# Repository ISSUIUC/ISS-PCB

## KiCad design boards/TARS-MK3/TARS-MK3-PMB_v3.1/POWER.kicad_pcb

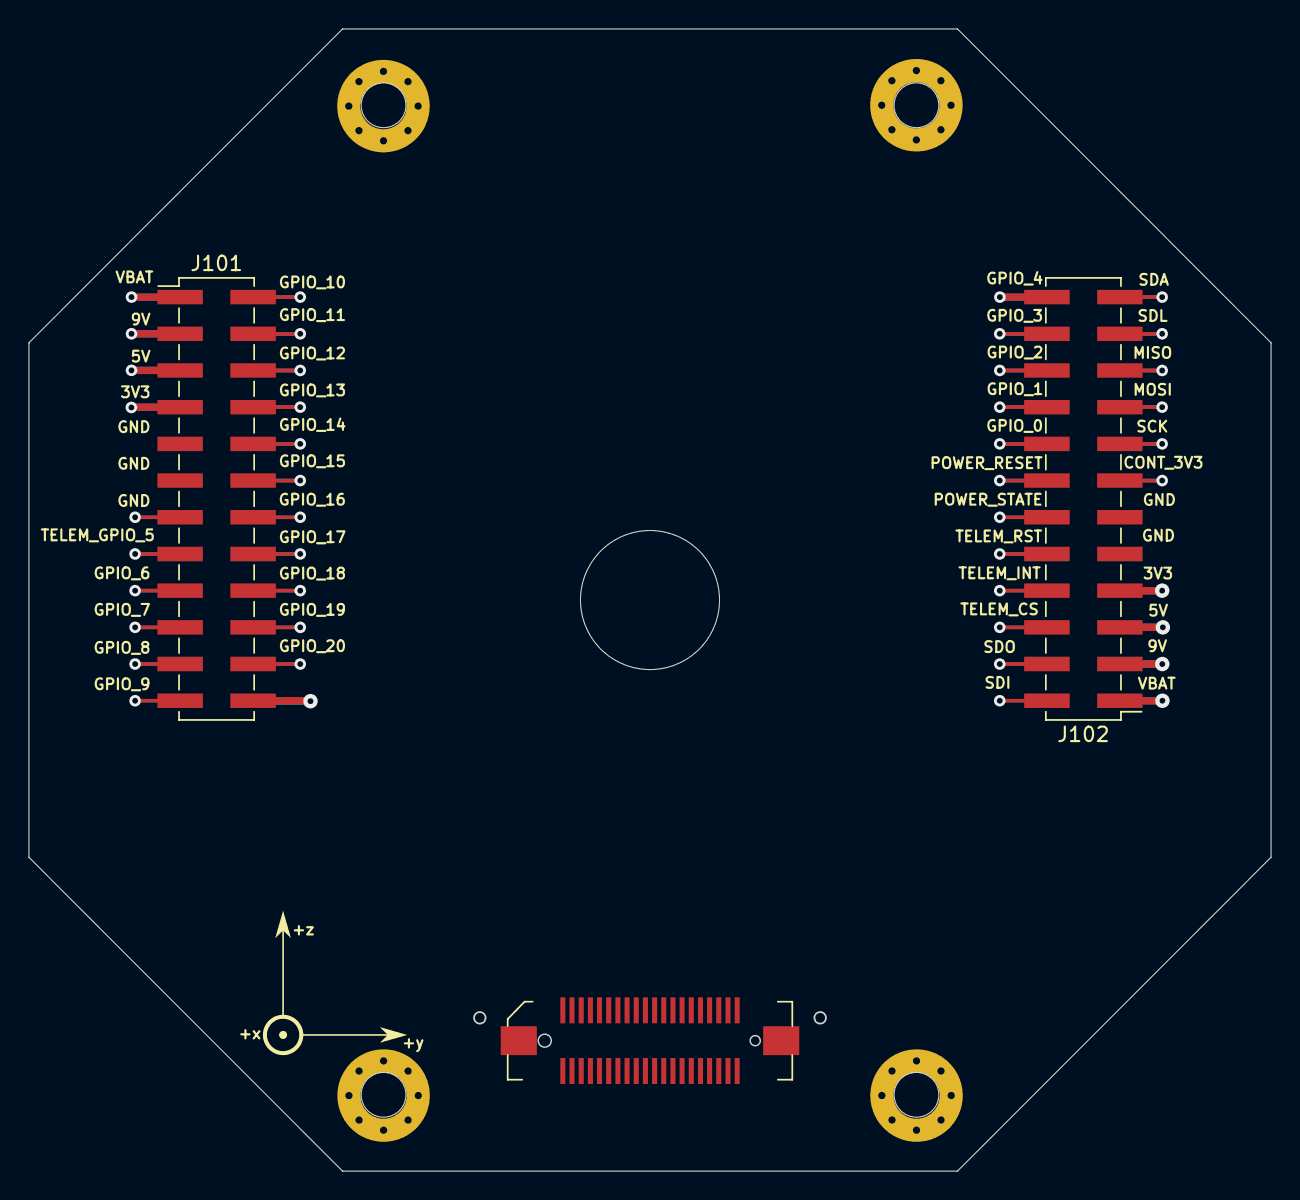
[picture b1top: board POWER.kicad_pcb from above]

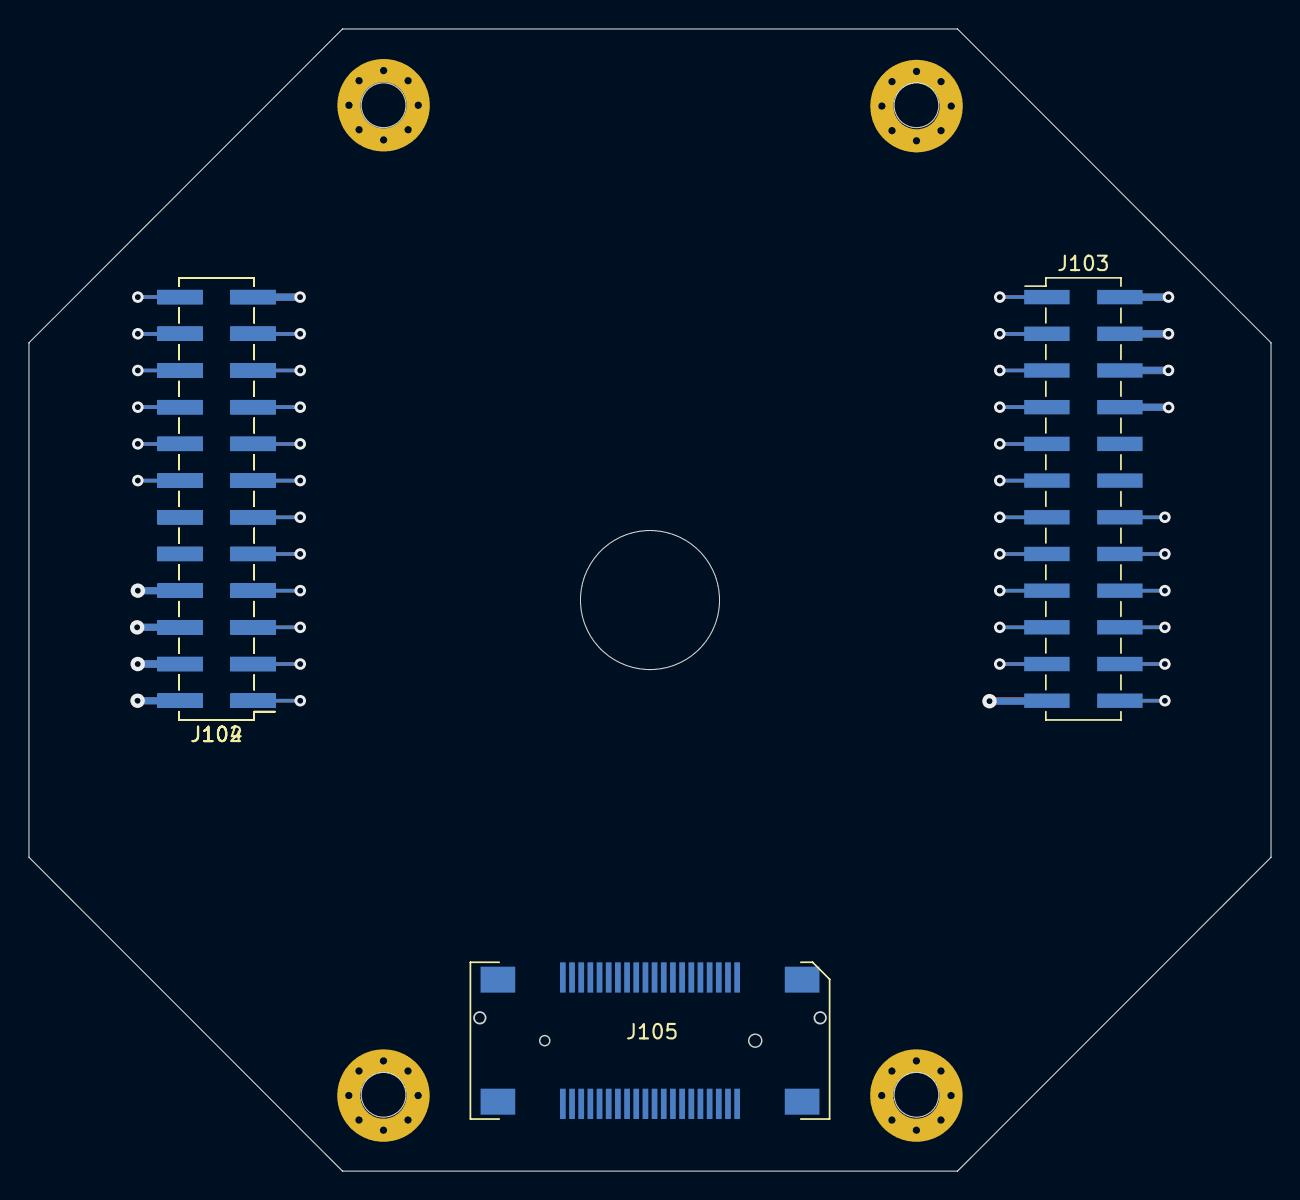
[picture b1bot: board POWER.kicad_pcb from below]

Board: 2 copper layers, 86.0 x 79.1 mm, 7 parts (4 on the bottom side), 41 nets.

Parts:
J101, J102, J102#2, J103, J104: Conn_02x12_Odd_Even; PinHeader_2x12_P2.54mm_Vertical_SMD
J105: Receptacle; 2091680401
J106: 536270474

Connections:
6V_AC_SERVO1: J102.24, J102#2.23, J104.23
6V_AC_SERVO2: J101.24, J103.23
/3V3: J101.7, J102.7, J102#2.8, J103.8, J104.8
/5V: J101.5, J102.5, J102#2.6, J103.6, J104.6
/9V: J101.3, J102.3, J102#2.4, J103.4, J104.4
/B2B_GPIO_8: J101.21, J103.22
/B2B_GPIO_9: J101.23, J103.24
/B2B_GPIO_10: J101.2, J103.1
/B2B_GPIO_11: J101.4, J103.3
/B2B_GPIO_12: J101.6, J103.5
/B2B_GPIO_13: J101.8, J103.7
/B2B_GPIO_14: J101.10, J103.9
/B2B_GPIO_15: J101.12, J103.11
/B2B_GPIO_16: J101.14, J103.13
/B2B_GPIO_17: J101.16, J103.15
/B2B_GPIO_18: J101.18, J103.17
/B2B_GPIO_19: J101.20, J103.19
/B2B_GPIO_20: J101.22, J103.21
/B2B_I2C_SCL: J102.21, J102#2.22, J104.22
/B2B_I2C_SDA: J102.23, J102#2.24, J104.24
/B2B_SPI_MISO: J102.19, J102#2.20, J104.20
/B2B_SPI_MOSI: J102.17, J102#2.18, J104.18
/B2B_SPI_SCK: J102.15, J102#2.16, J104.16
/B2B_UART_SDI: J102.2, J102#2.1, J104.1
/B2B_UART_SDO: J102.4, J102#2.3, J104.3
/CONT_3V3: J102.13, J102#2.14, J104.14
/CONT_GND: J101.13, J103.14
/GND: J101.9, J101.11, J102.9, J102.11, J102#2.10, J102#2.12, J103.10, J103.12, J104.10, J104.12
/POWER_RESET: J102.14, J102#2.13, J104.13
/POWER_STATE: J102.12, J102#2.11, J104.11
/SERVO1: J101.17, J103.18
/SERVO2: J101.19, J103.20
/TELEM_CS: J102.6, J102#2.5, J104.5
/TELEM_GPIO_1: J102.16, J102#2.15, J104.15
/TELEM_GPIO_2: J102.18, J102#2.17, J104.17
/TELEM_GPIO_3: J102.20, J102#2.19, J104.19
/TELEM_GPIO_4: J102.22, J102#2.21, J104.21
/TELEM_GPIO_5: J101.15, J103.16
/TELEM_INT: J102.8, J102#2.7, J104.7
/TELEM_RST: J102.10, J102#2.9, J104.9
/VBAT: J101.1, J102.1, J102#2.2, J103.2, J104.2

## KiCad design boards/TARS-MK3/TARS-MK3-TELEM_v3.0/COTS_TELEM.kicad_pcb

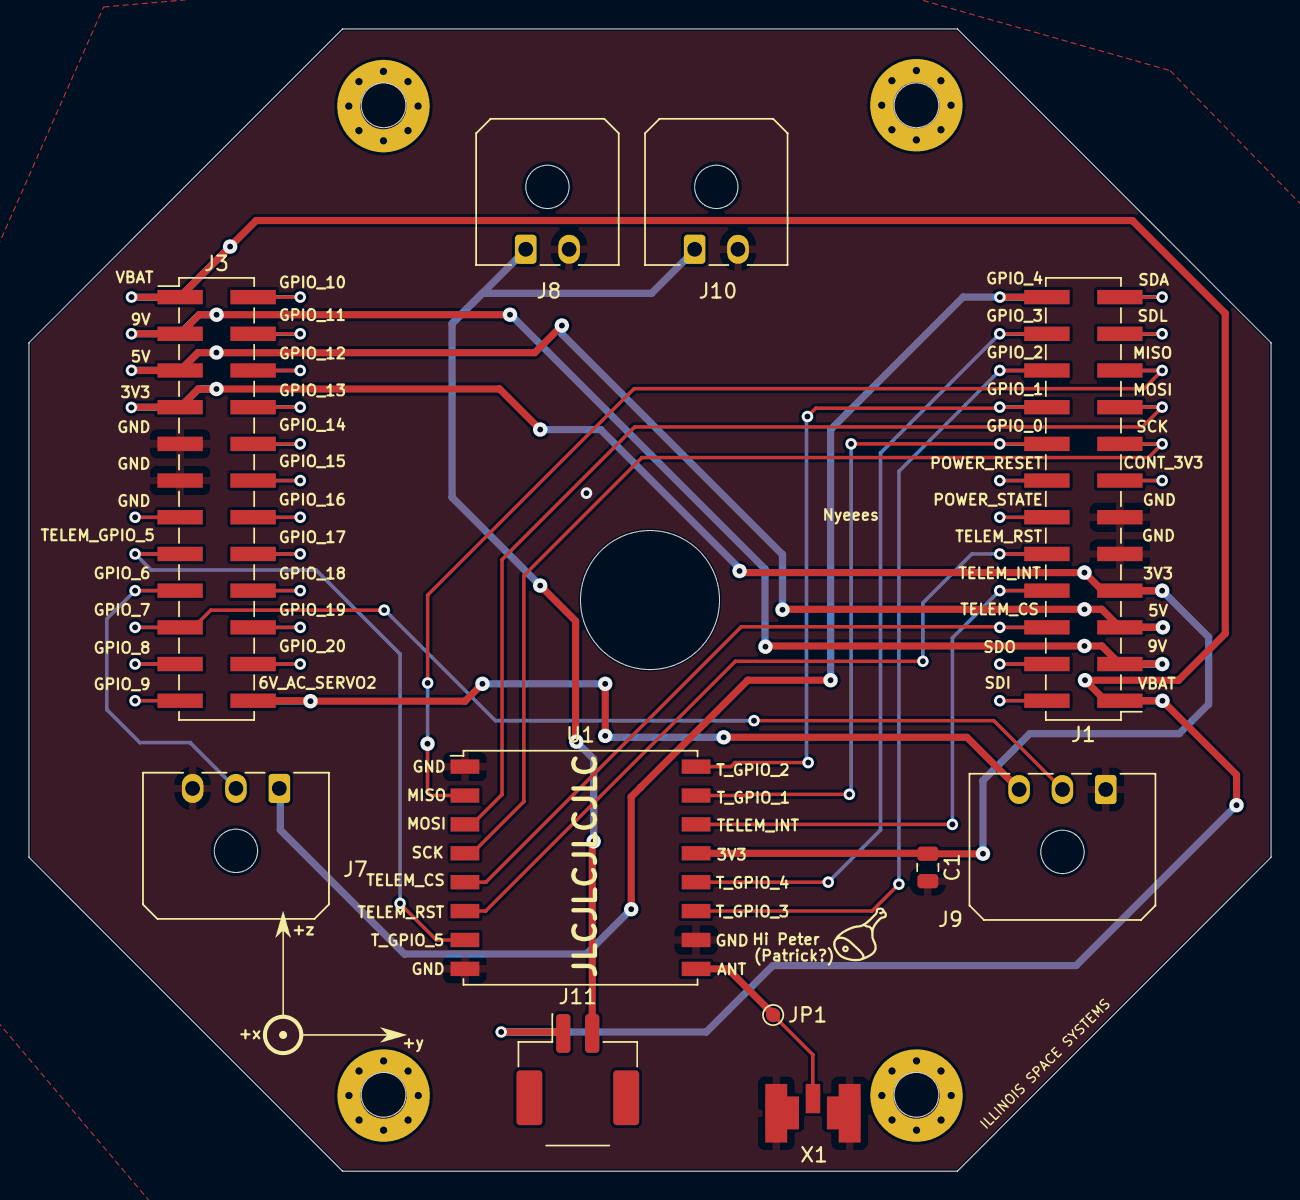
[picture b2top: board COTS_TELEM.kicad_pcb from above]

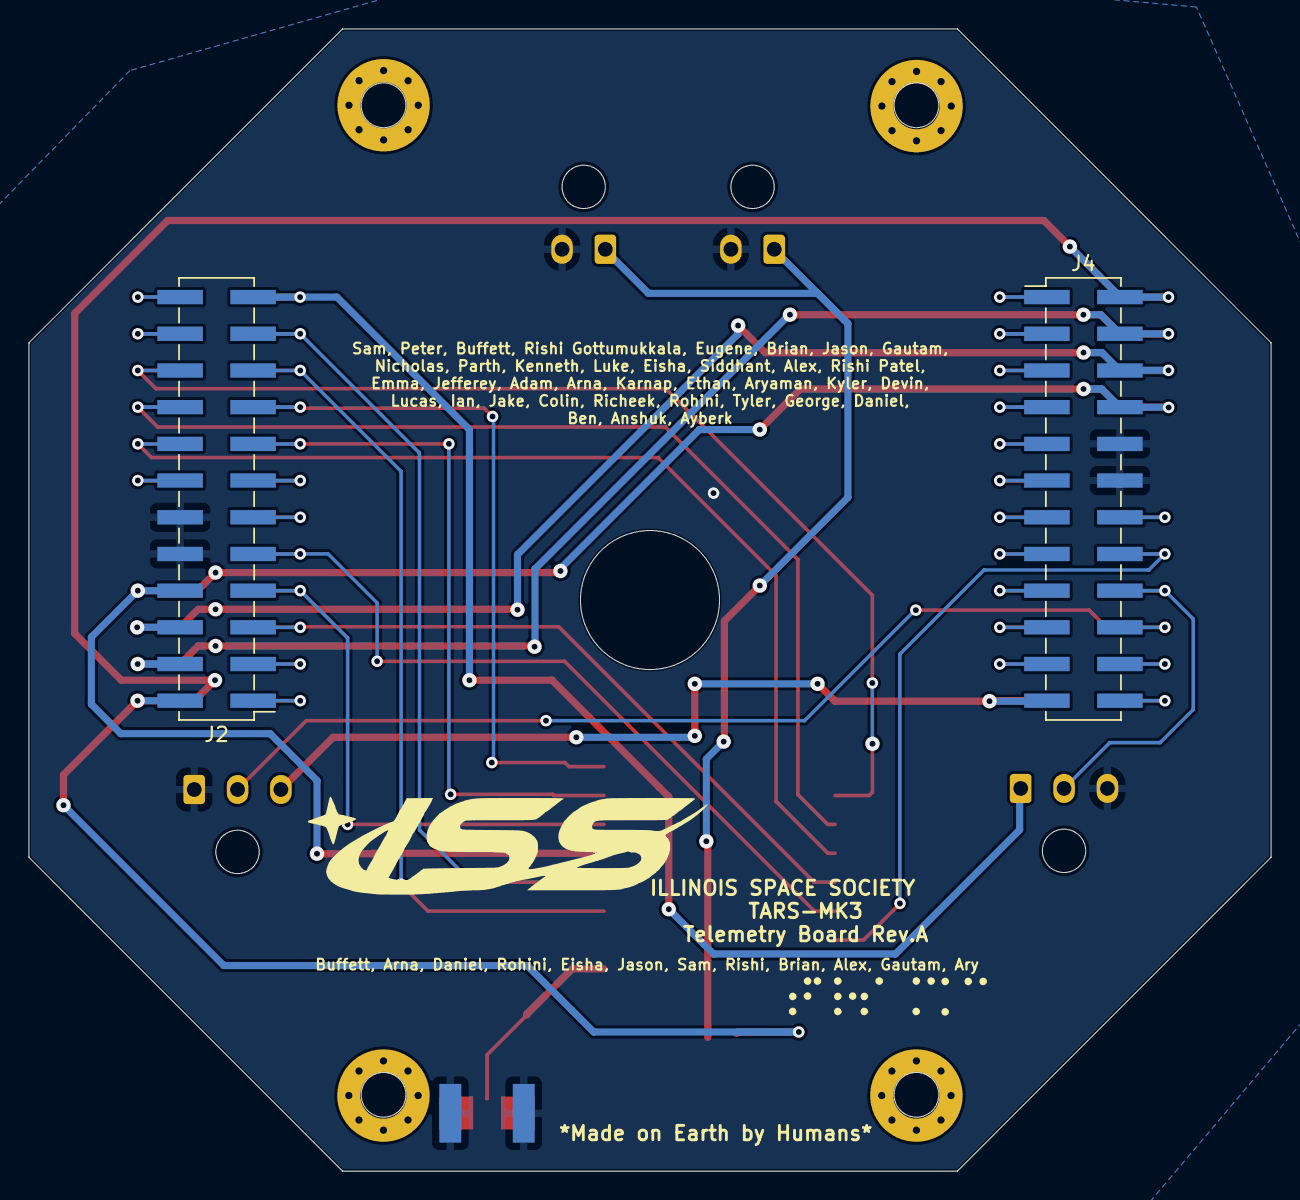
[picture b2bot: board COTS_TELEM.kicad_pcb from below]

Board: 2 copper layers, 86.0 x 79.1 mm, 13 parts (2 on the bottom side), 43 nets.

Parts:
C1: 10uF; C_0805_2012Metric
J1, J2, J3, J4: Conn_02x12_Odd_Even; PinHeader_2x12_P2.54mm_Vertical_SMD
J7, J9: Conn_01x03; Molex_Micro-Fit_3.0_43650-0300_1x03_P3.00mm_Horizontal
J8, J10: Conn_01x02; Molex_Micro-Fit_3.0_43650-0200_1x02_P3.00mm_Horizontal
J11: Conn_01x02; Molex_CLIK-Mate_502494-0270_1x02-1MP_P2.00mm_Horizontal
JP1: Conn_01x01_Female; TestPoint_Pad_D1.0mm
U1: RFM96W-433S2; HOPERF_RFM9XW_SMD
X1: uFL/SMA; uFL

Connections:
6V_AC_SERVO1: J1.24, J2.23, J7.1
6V_AC_SERVO2: J3.24, J4.23, J9.3
/3V3: C1.1, J1.7, J2.8, J3.7, J4.8, U1.13 (3.3V)
/5V: J1.5, J2.6, J3.5, J4.6
/9V: J1.3, J2.4, J3.3, J4.4
/B2B_GPIO_8: J3.21, J4.22
/B2B_GPIO_9: J3.23, J4.24
/B2B_GPIO_10: J3.2, J4.1
/B2B_GPIO_11: J3.4, J4.3
/B2B_GPIO_12: J3.6, J4.5
/B2B_GPIO_13: J3.8, J4.7
/B2B_GPIO_14: J3.10, J4.9
/B2B_GPIO_15: J3.12, J4.11
/B2B_GPIO_16: J3.14, J4.13
/B2B_GPIO_17: J3.16, J4.15
/B2B_GPIO_18: J3.18, J4.17
/B2B_GPIO_19: J3.20, J4.19
/B2B_GPIO_20: J3.22, J4.21
/B2B_I2C_SCL: J1.21, J2.22
/B2B_I2C_SDA: J1.23, J2.24
/B2B_SPI_MISO: J1.19, J2.20, U1.2 (MISO)
/B2B_SPI_MOSI: J1.17, J2.18, U1.3 (MOSI)
/B2B_SPI_SCK: J1.15, J2.16, U1.4 (SCK)
/B2B_UART_SDI: J1.2, J2.1
/B2B_UART_SDO: J1.4, J2.3
/CONT_3V3: J1.13, J2.14
/CONT_GND: J3.13, J4.14
/POWER_RESET: J1.14, J2.13
/POWER_STATE: J1.12, J2.11
/SERVO1: J3.17, J4.18, J7.2
/SERVO2: J3.19, J4.20, J9.2
/TELEM_CS: J1.6, J2.5, U1.5 (NSS)
/TELEM_GPIO_1: J1.16, J2.15, U1.15 (DIO1)
/TELEM_GPIO_2: J1.18, J2.17, U1.16 (DIO2)
/TELEM_GPIO_3: J1.20, J2.19, U1.11 (DIO3)
/TELEM_GPIO_4: J1.22, J2.21, U1.12 (DIO4)
/TELEM_GPIO_5: J3.15, J4.16, U1.7 (DIO5)
/TELEM_INT: J1.8, J2.7, U1.14 (DIO0)
/TELEM_RST: J1.10, J2.9, U1.6 (RESET)
/VBAT: J1.1, J2.2, J3.1, J4.2, J11.1
GND: C1.2, J1.9, J1.11, J2.10, J2.12, J3.9, J3.11, J4.10, J4.12, J7.3, J8.2, J9.1, J10.2, U1.1 (GND), U1.8 (GND), U1.10 (GND), X1.GND1, X1.GND2, X1.GND3, X1.GND4
unnamed: J8.1, J10.1, J11.2
unnamed: JP1.1, U1.9 (ANT), X1.ANTENNA (ANT)

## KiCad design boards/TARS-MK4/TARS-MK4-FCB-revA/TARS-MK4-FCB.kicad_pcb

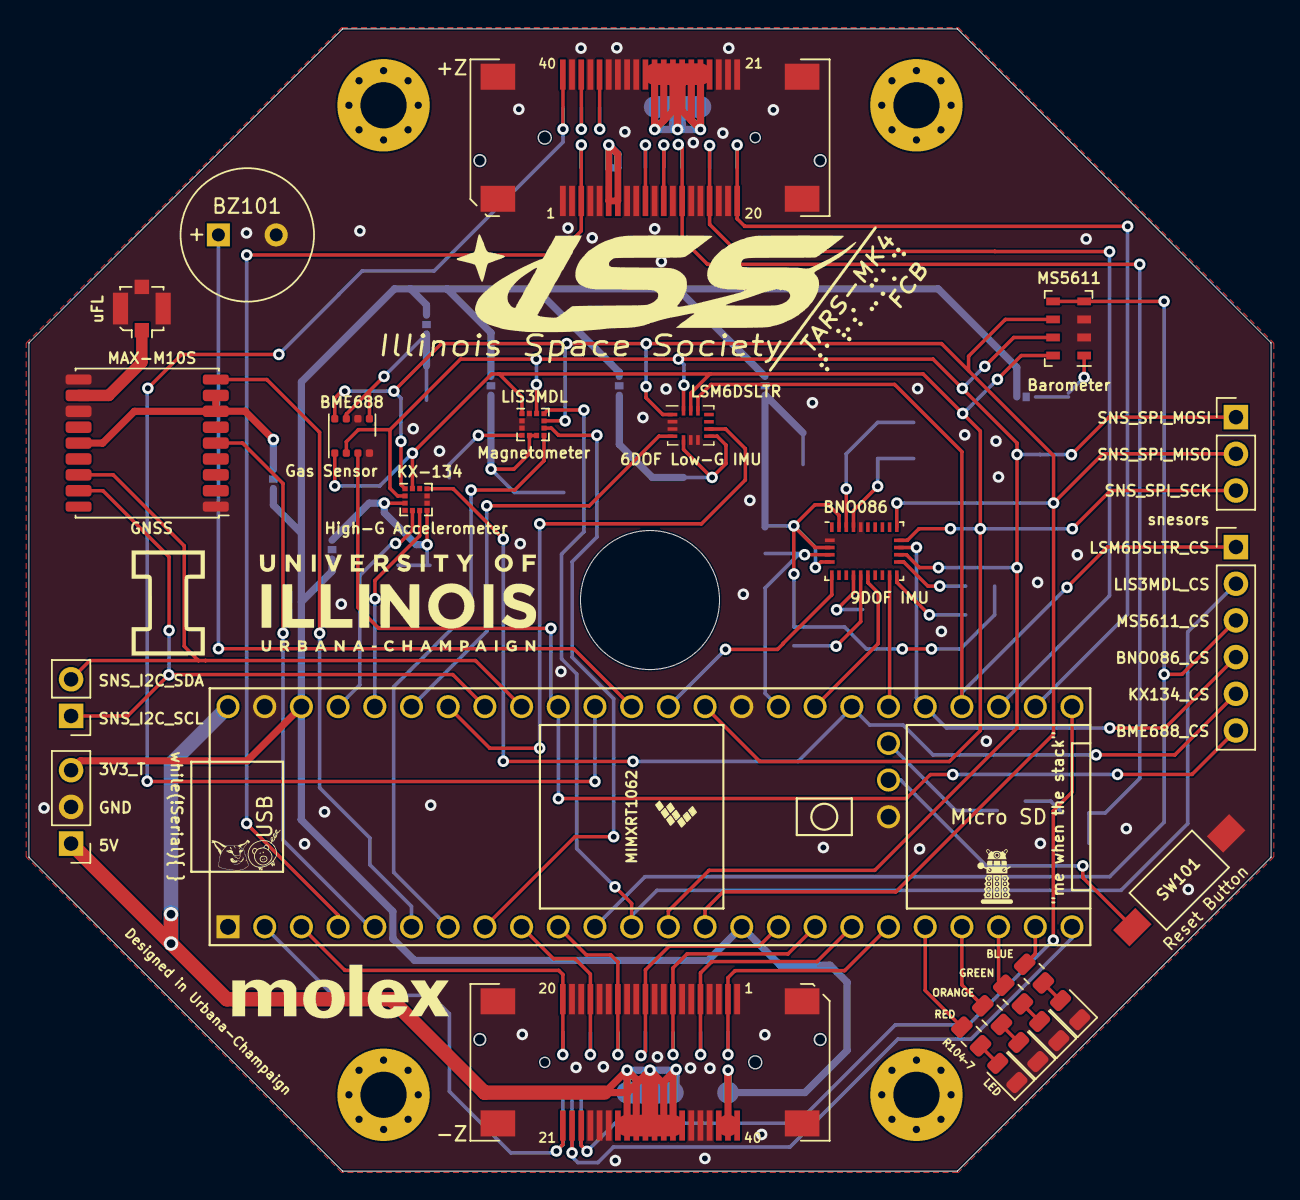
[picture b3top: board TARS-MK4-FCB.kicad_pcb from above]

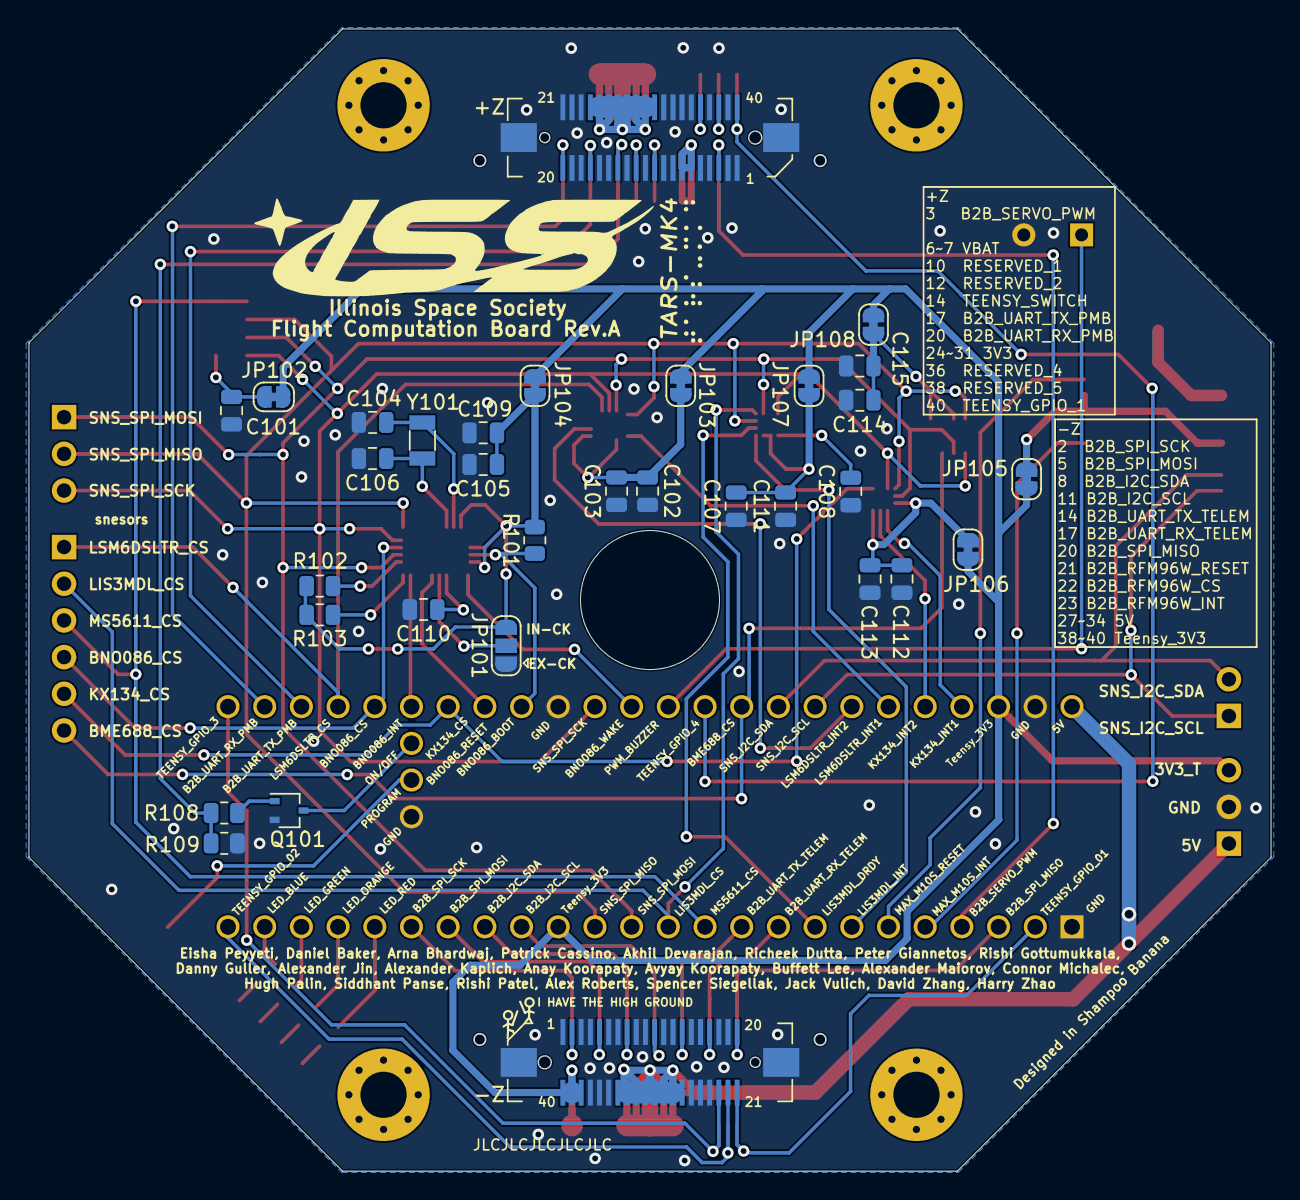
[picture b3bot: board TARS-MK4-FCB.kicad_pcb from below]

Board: 2 copper layers, 86.0 x 79.1 mm, 57 parts (32 on the bottom side), 74 nets.

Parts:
BZ101: Buzzer; MagneticBuzzer_PUI_AT-0927-TT-6-R
C101, C102, C103, C105, C109, C110, C112, C113, C114, C115: 0.1uF; C_0805_2012Metric
C104, C106: 22pF; C_0805_2012Metric
C107: 1uF; C_0805_2012Metric
C108, C111: 100nF; C_0805_2012Metric
D101: RED LED; LED_0805_2012Metric
D102: ORANGE LED; LED_0805_2012Metric
D103: GREEN LED; LED_0805_2012Metric
D104: BLUE LED; LED_0805_2012Metric
J101: U.FL; U.FL_Molex_MCRF_73412-0110_Vertical
J102, J103: Molex_SlimStack_2091680401_2x20_P0.635mm; Molex_SlimStack_Receptacle_2091680401_2x20_P0.635mm
J104, J105: Molex_SlimStack_Plug_2x20_P0.365mm; Molex_SlimStack_Plug_536270474_2x20_P0.365mm
J106, J109: Conn_01x03; PinHeader_1x03_P2.54mm_Vertical
J107: Conn_01x02; PinHeader_1x02_P2.54mm_Vertical
J108: Conn_01x06; PinHeader_1x06_P2.54mm_Vertical
JP101: SolderJumper_3_Open; SolderJumper-3_P1.3mm_Open_RoundedPad1.0x1.5mm
JP102, JP105, JP106, JP108: Jumper_NC_Small; SolderJumper-2_P1.3mm_Bridged_RoundedPad1.0x1.5mm
JP103, JP104, JP107: Jumper_2_Bridged; SolderJumper-2_P1.3mm_Bridged_RoundedPad1.0x1.5mm
Q101: SSM3K16FU; SOT-323_SC-70
R101: 10k; R_0805_2012Metric
R102, R103: 2.2k; R_0805_2012Metric
R104, R105, R106, R107: 470; R_0805_2012Metric
R108: 100K; R_0805_2012Metric
R109: 100; R_0805_2012Metric
SW101: FSMSM Switch; SW_SPST_FSMSM
U101: MS5611-01BA03; LGA-8_3x5mm_P1.25mm
U102: LSM6DSLTR; Bosch_LGA-14_3x2.5mm_P0.5mm
U103: MAX-M10S; ublox_MAX
U104: BNO086; LGA-28_5.2x3.8mm_P0.5mm
U105: LIS3MDL; LGA-12_2x2mm_P0.5mm
U106: KX134-1211; LGA-12_2x2mm_P0.5mm
U107: Teensy4.1; Teensy41
U108: BME688; Bosch_LGA-8_3x3mm_P0.8mm_ClockwisePinNumbering
Y101: 32.768kHz; Crystal_SMD_3215-2Pin_3.2x1.5mm

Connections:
/3V3: J102.24, J102.25, J102.26, J102.27, J102.28, J102.29, J102.30, J102.31, J104.24, J104.25, J104.26, J104.27, J104.28, J104.29, J104.30, J104.31
/5V: J103.27, J103.28, J103.29, J103.30, J103.31, J103.32, J103.33, J103.34, J105.27, J105.28, J105.29, J105.30, J105.31, J105.32, J105.33, J105.34, J109.1, U107.48 (VIN)
/B2B_I2C_SCL: J103.11, J105.11, U107.16 (24_A10_TX6_SCL2)
/B2B_I2C_SDA: J103.8, J105.8, U107.17 (25_A11_RX6_SDA2)
/B2B_RFM96W_CS: J103.22, J105.22, U107.24 (32_OUT1B)
/B2B_RFM96W_INT: J103.23, J105.23, U107.25 (33_MCLK2)
/B2B_RFM96W_RESET: J103.21, J105.21, U107.2 (0_RX1_CRX2_CS1)
/B2B_SERVO_PWM: J102.3, J104.3, U107.4 (2_OUT2)
/B2B_SPI_MISO: J103.20, J105.20, U107.3 (1_TX1_CTX2_MISO1)
/B2B_SPI_MOSI: J103.5, J105.5, U107.18 (26_A12_MOSI1)
/B2B_SPI_SCK: J103.2, J105.2, U107.19 (27_A13_SCK1)
/B2B_UART_RX_PMB: J102.20, J104.20, U107.26 (34_RX8)
/B2B_UART_RX_TELEM: J103.17, J105.17, U107.9 (7_RX2_OUT1A)
/B2B_UART_TX_PMB: J102.17, J104.17, U107.27 (35_TX8)
/B2B_UART_TX_TELEM: J103.14, J105.14, U107.10 (8_TX2_IN1)
/BME688_CS: J108.6, U107.39 (17_A3_TX4_SDA1), U108.2 (CSB)
/BNO086_BOOT: R101.1, U104.4 (BOOTN), U107.33 (41_A17)
/BNO086_CS: J108.4, U104.18 (H_CSN), U107.29 (37_CS)
/BNO086_INT: U104.14 (H_INTN), U107.30 (38_CS1_IN1)
/BNO086_RESET: U104.11 (NRST), U107.32 (40_A16)
/BNO086_WAKE: U104.6 (PS0/WAKE), U107.36 (14_A0_TX3_SPDIF_OUT)
/KX134_CS: J108.5, U106.10 (nCS), U107.31 (39_MISO1_OUT1A)
/KX134_INT1: U106.5 (INT1), U107.45 (23_A9_CRX1_MCLK1)
/KX134_INT2: U106.6 (INT2), U107.44 (22_A8_CTX1)
/LED_BLUE: R107.1, U107.23 (31_CTX3)
/LED_GREEN: R106.1, U107.22 (30_CRX3)
/LED_ORANGE: R105.1, U107.21 (29_TX7)
/LED_RED: R104.1, U107.20 (28_RX7)
/LIS3MDL_CS: J108.2, U105.10 (CS), U107.12 (10_CS_MQSR)
/LIS3MDL_DRDY: U105.8 (DRDY), U107.8 (6_OUT1D)
/LIS3MDL_INT: U105.7 (INT), U107.7 (5_IN2)
/LSM6DSLTR_CS: J108.1, U102.12 (CS), U107.28 (36_CS)
/LSM6DSLTR_INT1: U102.4 (INT1), U107.43 (21_A7_RX5_BCLK1)
/LSM6DSLTR_INT2: U102.9 (INT2), U107.42 (20_A6_TX5_LRCLK1)
/MAX-M10S_INT: U103.5 (EXTINT), U107.5 (3_LRCLK2)
/MAX-M10S_RESET: U103.9 (RESET_N), U107.6 (4_BCLK2)
/MS5611_CS: J108.3, U101.4 (CSB), U101.5 (CSB), U107.11 (9_OUT1C)
/PROGRAM: SW101.1, U107.53 (PROGRAM)
/PWM_BUZZER: BZ101.1 (-), U107.37 (15_A1_RX3_SPDIF_IN)
/RESERVED_1: J102.10, J104.10
/RESERVED_2: J102.12, J104.12
/RESERVED_3: J102.36, J104.36
/RESERVED_4: J102.38, J104.38
/SNS_I2C_SCL: J107.1, U103.17 (SCL), U107.41 (19_A5_SCL)
/SNS_I2C_SDA: J107.2, U103.16 (SDA), U107.40 (18_A4_SDA)
/SNS_SPI_MISO: J106.2, U101.6 (SDO), U102.1 (SDO/SA0), U104.20 (H_SDA/H_MISO/TX), U105.9 (SDO/SA1), U106.1 (SDO/ADDR), U107.14 (12_MISO_MQSL), U108.5 (SDO)
/SNS_SPI_MOSI: J106.1, U101.7 (SDI/SDA), U102.14 (SDA), U104.17 (H_SA0_MOSI), U105.11 (SDA/SDI/SDO), U106.2 (SDI/SDA), U107.13 (11_MOSI_CTX1), U108.3 (SDI)
/SNS_SPI_SCK: J106.3, U101.8 (SCLK), U102.13 (SCL), U104.19 (H_SCL/SCK/RX), U105.1 (SCL/SPC), U106.12 (SCLK/SCL), U107.35 (13_SCK_LED), U108.4 (SCK)
/TEENSY_GPIO_1: J102.40, J104.40, U107.38 (16_A2_RX4_SCL1)
/TEENSY_ON/OFF: Q101.3 (D), U107.54 (On/Off)
/TEENSY_SWITCH: J102.14, J104.14, R108.1, R109.2
/Teensy_3V3: J103.38, J103.39, J103.40, J105.38, J105.39, J105.40, J109.3, JP102.1 (A), JP103.1 (A), JP104.2 (B), JP105.1 (A), JP106.1 (A), JP107.1 (A), JP108.1 (A), U107.15 (3V3), U107.46 (3V3)
/VBAT: J102.6, J102.7, J104.6, J104.7
GND: BZ101.2 (+), C101.1, C102.1, C103.1, C104.2, C105.2, C106.2, C107.1, C108.1, C109.2, C110.2, C111.1, C112.2, C113.1, C114.2, C115.1, D101.1 (K), D102.1 (K), D103.1 (K), D104.1 (K), J101.2 (Ext), J102.1, J102.2, J102.4, J102.5, J102.8, J102.9, J102.11, J102.13, J102.15, J102.16, J102.18, J102.19, J102.21, J102.22, J102.23, J102.32, J102.33, J102.34, J102.35, J102.37, J102.39, J102.GND, J103.1, J103.3, J103.4, J103.6, J103.7, J103.9, J103.10, J103.12, J103.13, J103.15, J103.16, J103.18, J103.19, J103.24, J103.25, J103.26, J103.35, J103.36, J103.37, J103.GND, J104.1, J104.2, J104.4, J104.5, J104.8, J104.9, J104.11, J104.13, J104.15, J104.16, J104.18, J104.19, J104.21, J104.22, J104.23, J104.32, J104.33, J104.34, J104.35, J104.37, J104.39, J104.GND, J105.1, J105.3, J105.4, J105.6, J105.7, J105.9, J105.10, J105.12, J105.13, J105.15, J105.16, J105.18, J105.19, J105.24, J105.25, J105.26, J105.35, J105.36, J105.37, J105.GND, J109.2, JP101.1 (A), Q101.2 (S), R108.2, SW101.2, U101.2 (PS), U101.3 (GND), U102.2 (SDX), U102.3 (SCX), U102.6 (GND), U102.7 (GND), U103.1 (GND), U103.10 (GND), U103.12 (GND), U104.2 (GND), U104.25 (GNDIO), U105.2 (GND), U105.3 (GND), U105.12 (GND), U106.4 (TRIG), U106.8 (GND), U106.9 (GND), U107.1 (GND), U107.34 (GND), U107.47 (GND), U107.52 (GND), U108.1 (GND), U108.7 (GND)
unnamed: C101.2, JP102.2 (B), U101.1 (VDD)
unnamed: C102.2, C103.2, JP103.2 (B), U102.5 (VDDIO), U102.8 (VDD)
unnamed: C104.1, U104.27 (XIN32), Y101.1
unnamed: C105.1, C109.1, JP101.3 (B), JP104.1 (A), R101.2, R102.2, R103.2, U104.3 (VDD), U104.5 (PS1), U104.28 (VDDIO)
unnamed: C106.1, U104.26 (XOUT32/CLKSEL1), Y101.2
unnamed: C107.2, C111.2, JP107.2 (B), U105.5 (VDD), U105.6 (VDD_IO)
unnamed: C108.2, U105.4 (C1)
unnamed: C110.1, U104.9 (CAP)
unnamed: C112.1, C113.2, JP106.2 (B), U106.3 (VDDIO), U106.7 (VDD)
unnamed: C114.1, C115.2, JP108.2 (B), U108.6 (VDDIO), U108.8 (VDD)
unnamed: D101.2 (A), R104.2
unnamed: D102.2 (A), R105.2
unnamed: D103.2 (A), R106.2
unnamed: D104.2 (A), R107.2
unnamed: J101.1 (In), U103.11 (RF_IN)
unnamed: JP101.2 (C), U104.10 (CLKSEL0)
unnamed: JP105.2 (B), U103.7 (V_IO), U103.8 (VCC), U103.14 (VCC_RF)
unnamed: Q101.1 (G), R109.1
unnamed: R102.1, U104.16 (ENV_SDA)
unnamed: R103.1, U104.15 (ENV_SCL)
